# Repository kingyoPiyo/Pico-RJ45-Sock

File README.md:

# Pico-RJ45-Sock

RJ45 connector for Raspberry Pi Pico.  
10BASE-T communication using Raspberry Pi Pico's PIO and software stack.  
See also : [Pico-10BASE-T](https://github.com/kingyoPiyo/Pico-10BASE-T "Pico-10BASE-T")

## Board Layout

## Assembly

## Schematic
[pico_rj45.pdf](kicad/pico_rj45.pdf "Schematic")

## Sample Firmware
| Link | Description |
| ---- | ---- |
| [Hello World](firmware/hello_world/ "hello_world") | ARP, UDP, ICMP Test.<br>Change *system.h* for connection settings.|
| [VBAN](firmware/vban/ "vban") | ARP, UDP, ICMP & VBAN Audio Streaming from ADC0, ADC1.<br>Change *system.h* for connection settings.<br>Please refer [here](doc/vban_preamp/VBAN_PreAmp.png "VBAN_PreAmp.png") for the preamplifier for ADC.|

## Quick-start

### pico-sdk install
See also : https://github.com/raspberrypi/pico-sdk
```
sudo apt install cmake gcc-arm-none-eabi libnewlib-arm-none-eabi libstdc++-arm-none-eabi-newlib build-essential
git clone https://github.com/raspberrypi/pico-sdk
cd pico-sdk
git submodule update --init
```
### Hello world Compile
```
git clone https://github.com/kingyopiyo/Pico-RJ45-Sock
cd Pico-RJ45-Sock/firmware/hello_world
mkdir build
cd build
cmake ..
make
```

## Reference
* Pico DVI Sock https://github.com/Wren6991/Pico-DVI-Sock
* pico_eth https://github.com/holysnippet/pico_eth_doc

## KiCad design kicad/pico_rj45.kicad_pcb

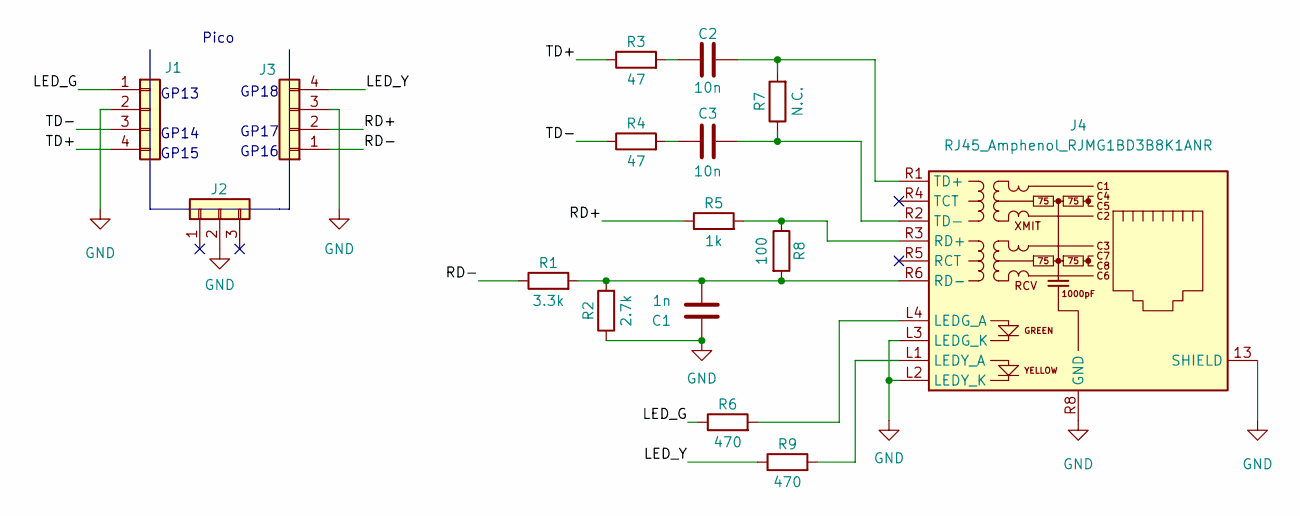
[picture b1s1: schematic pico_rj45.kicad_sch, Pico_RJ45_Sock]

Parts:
C1: 1n; C_0603_1608Metric
C2, C3: 10n; C_0603_1608Metric
J1, J3: Conn_01x04; castellated_2.54mm_smd_x4
J2: Conn_01x03; castellated_2.54mm_smd_x3
J4: RJ45_Amphenol_RJMG1BD3B8K1ANR
R1: 3.3k; R_0603_1608Metric
R2: 2.7k; R_0603_1608Metric
R3, R4: 47; R_0603_1608Metric
R5: 1k; R_0603_1608Metric
R6, R9: 470; R_0603_1608Metric
R7: N.C.; R_0603_1608Metric
R8: 100; R_0603_1608Metric

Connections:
/LED_G: J1.1, R6.1
/LED_Y: J3.4, R9.1
/RD+: J3.2, R5.1
/RD-: J3.1, R1.1
/TD+: J1.4, R3.1
/TD-: J1.3, R4.1
GND: C1.1, J1.2, J2.2, J3.3, J4.13 (SHIELD), J4.L2 (LEDY_K), J4.L3 (LEDG_K), J4.R8 (GND), R2.1
unnamed: C1.2, J4.R6 (RD-), R1.2, R2.2, R8.2
unnamed: C2.2, R3.2
unnamed: C3.2, R4.2
unnamed: J4.L1 (LEDY_A), R9.2
unnamed: J4.L4 (LEDG_A), R6.2
unnamed: C2.1, J4.R1 (TD+), R7.2
unnamed: C3.1, J4.R2 (TD-), R7.1
unnamed: J4.R3 (RD+), R5.2, R8.1

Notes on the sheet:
GP13
GP17
GP16
GP15
Pico
GP14
GP18

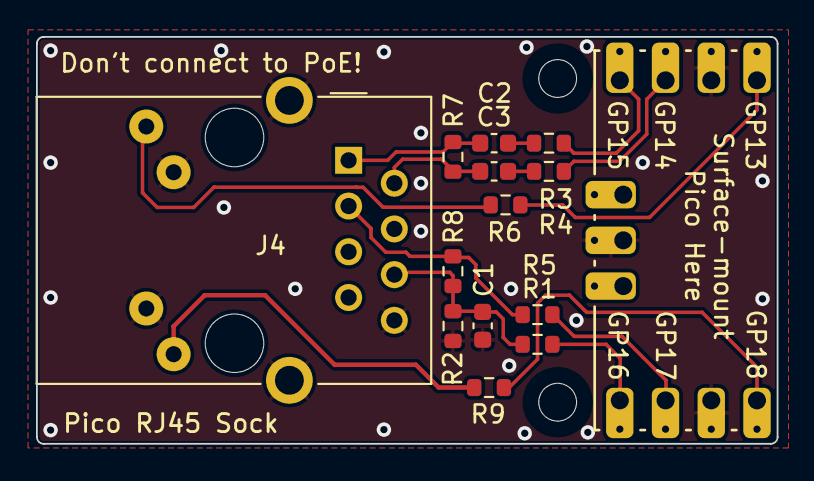
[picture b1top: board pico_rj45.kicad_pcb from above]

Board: 2 copper layers, 41.1 x 22.6 mm, 16 parts (0 on the bottom side), 15 nets.

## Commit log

2023-01-09 Add some files
2023-03-27 Add some files..
2023-12-10 Use DMA for CRC Calc
2023-12-10 DMA対応
2023-12-10 Linkパルスの送信タイミング他改善
2023-12-10 PIOクロックの分周設定値を自動計算するようにした
2023-12-10 コンパイルエーラ対策
2023-12-28 clean up
2023-12-28 Add ip address filter
2024-03-16 TX pin drive strength up.
2024-03-16 Bug fix.
2024-03-16 Add IFG
2024-03-16 とりあえず動作
2024-03-16 ADCのバッファをリングバッファに変更
2024-03-17 Add OLED code
2024-04-08 Add Schematic.
2024-08-16 Add include file : clocks.h
